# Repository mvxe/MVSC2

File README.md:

# MVSC2 - MV Stepper Controller V2 

Stepper controller using a STM32F411CEU6 and 6x TMC2208-LA-T.  
Intended as a 3D printer controller, or a standalone 6 stepper driver.  
Also has 6 connectors for endstops or servos.  
Includes design with magnetic proximity sensors as endstops using CH912LSR.  

Design files ready for production at JLCPCB (except connectors, TODO).  

NOTE:  
- In the design I use a lower current setting for the stepper driver, which is meant for weaker steppers. Change sense resistor for normal stepper.  
- It is mean to be attached to a 2040 V slot profile, for cooling.  
- Since fabricating this, JLCPCB now supports connectors so this should be updated (hand soldering a USBC is not fun).  
- The power connector requires hand modification: the leads should be shortened such, and the support pins as well as not to portrude from the other side. Apply superglue for extra strength.  
- A compatible Marlin configuration to be added at a later date.

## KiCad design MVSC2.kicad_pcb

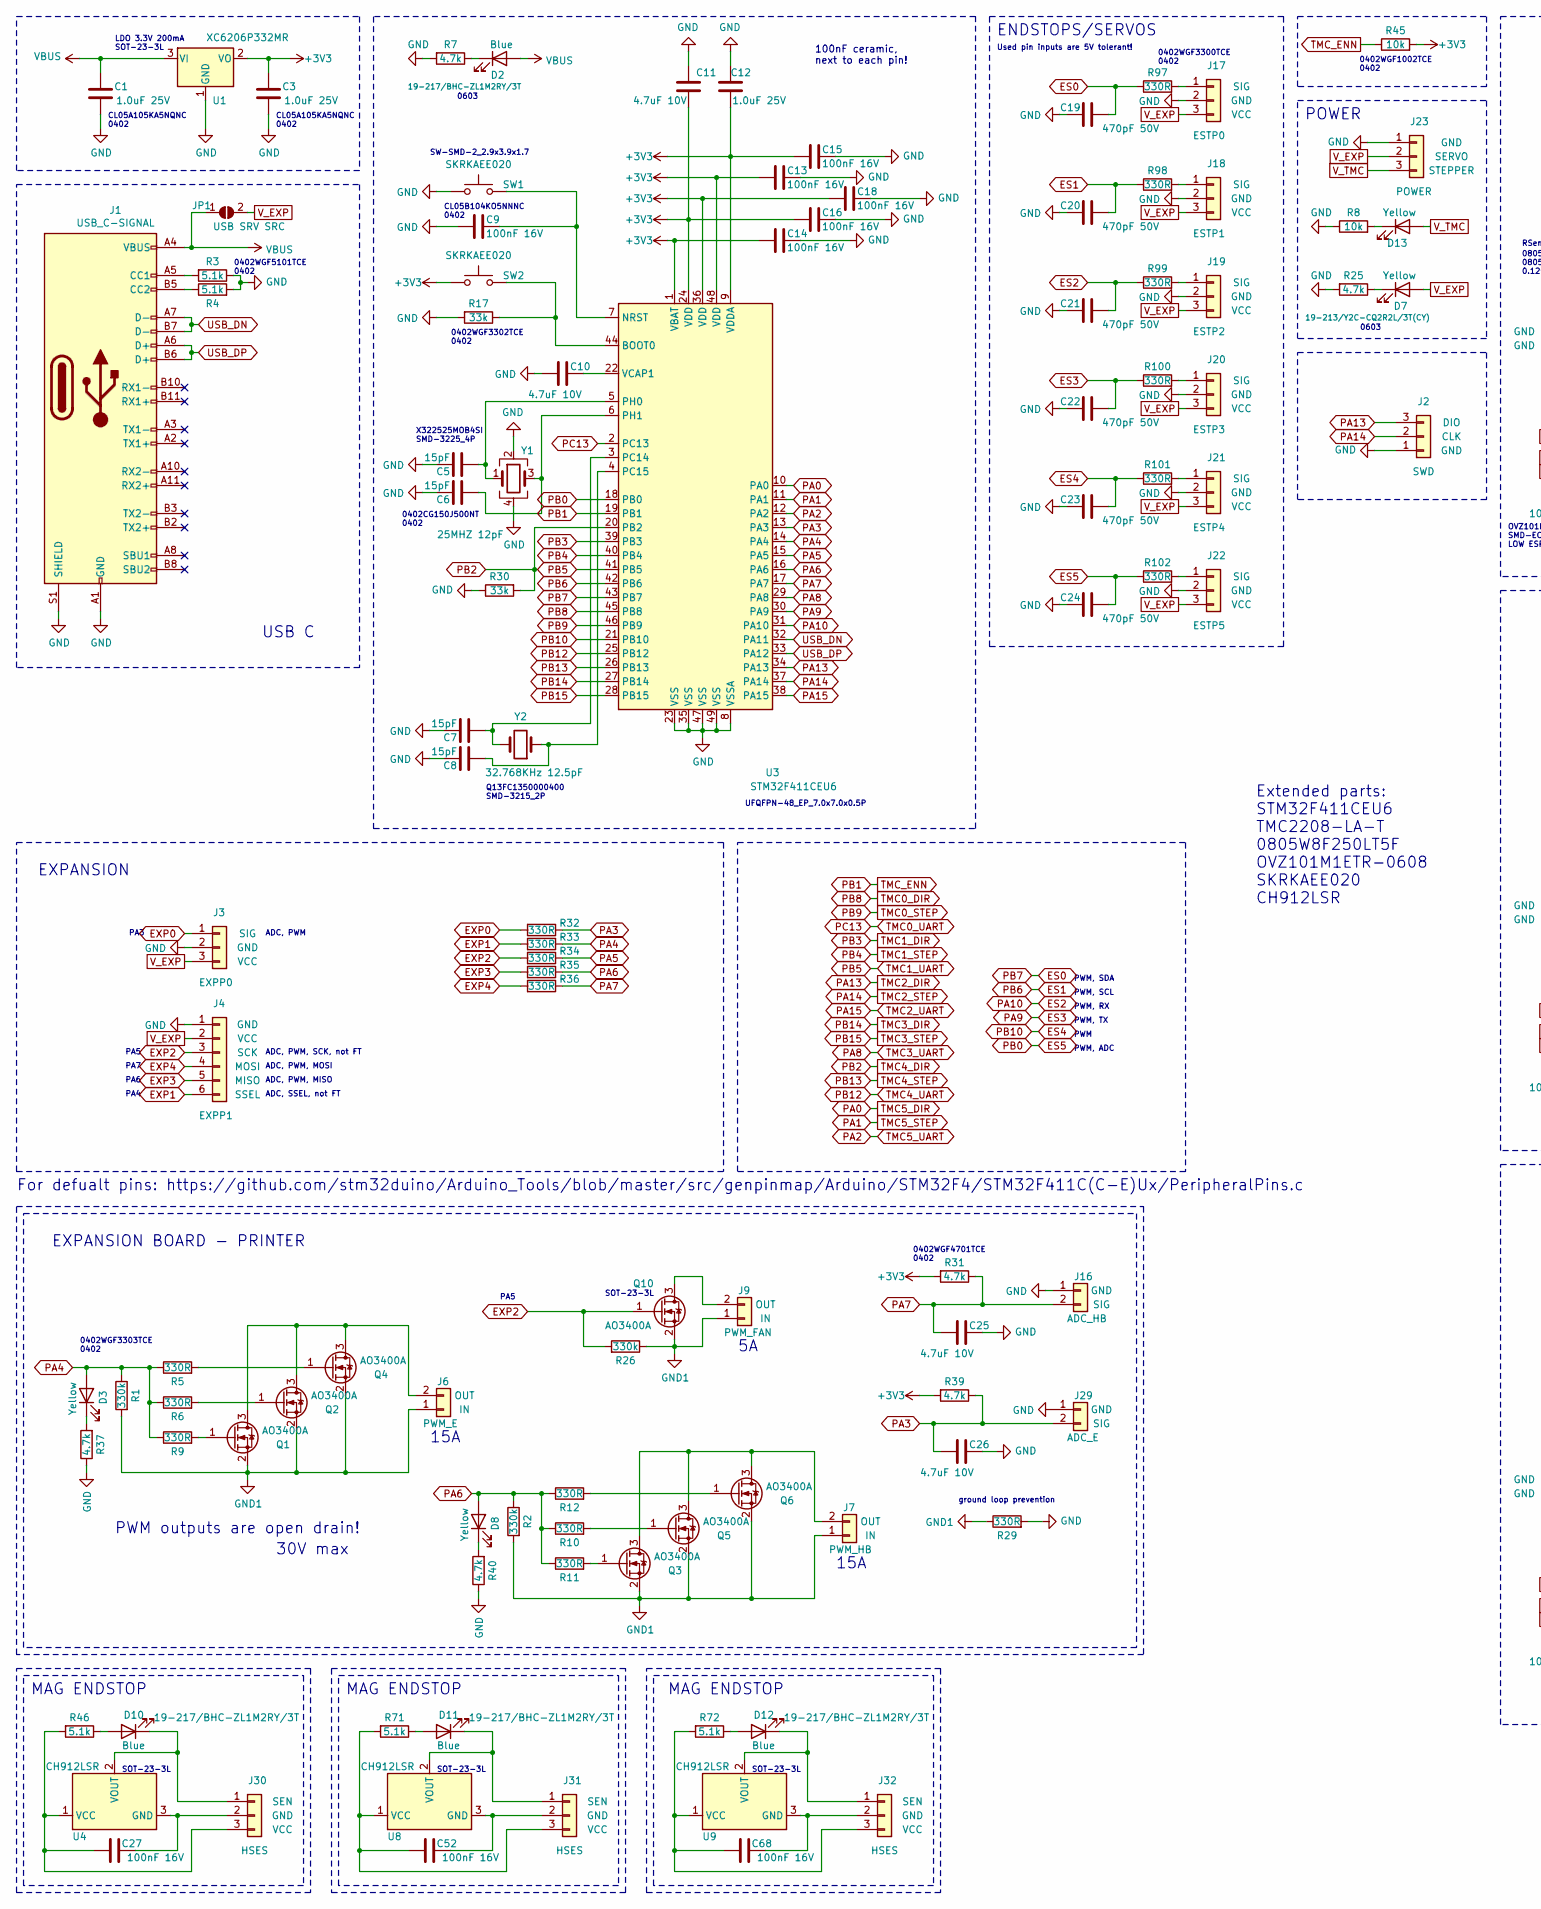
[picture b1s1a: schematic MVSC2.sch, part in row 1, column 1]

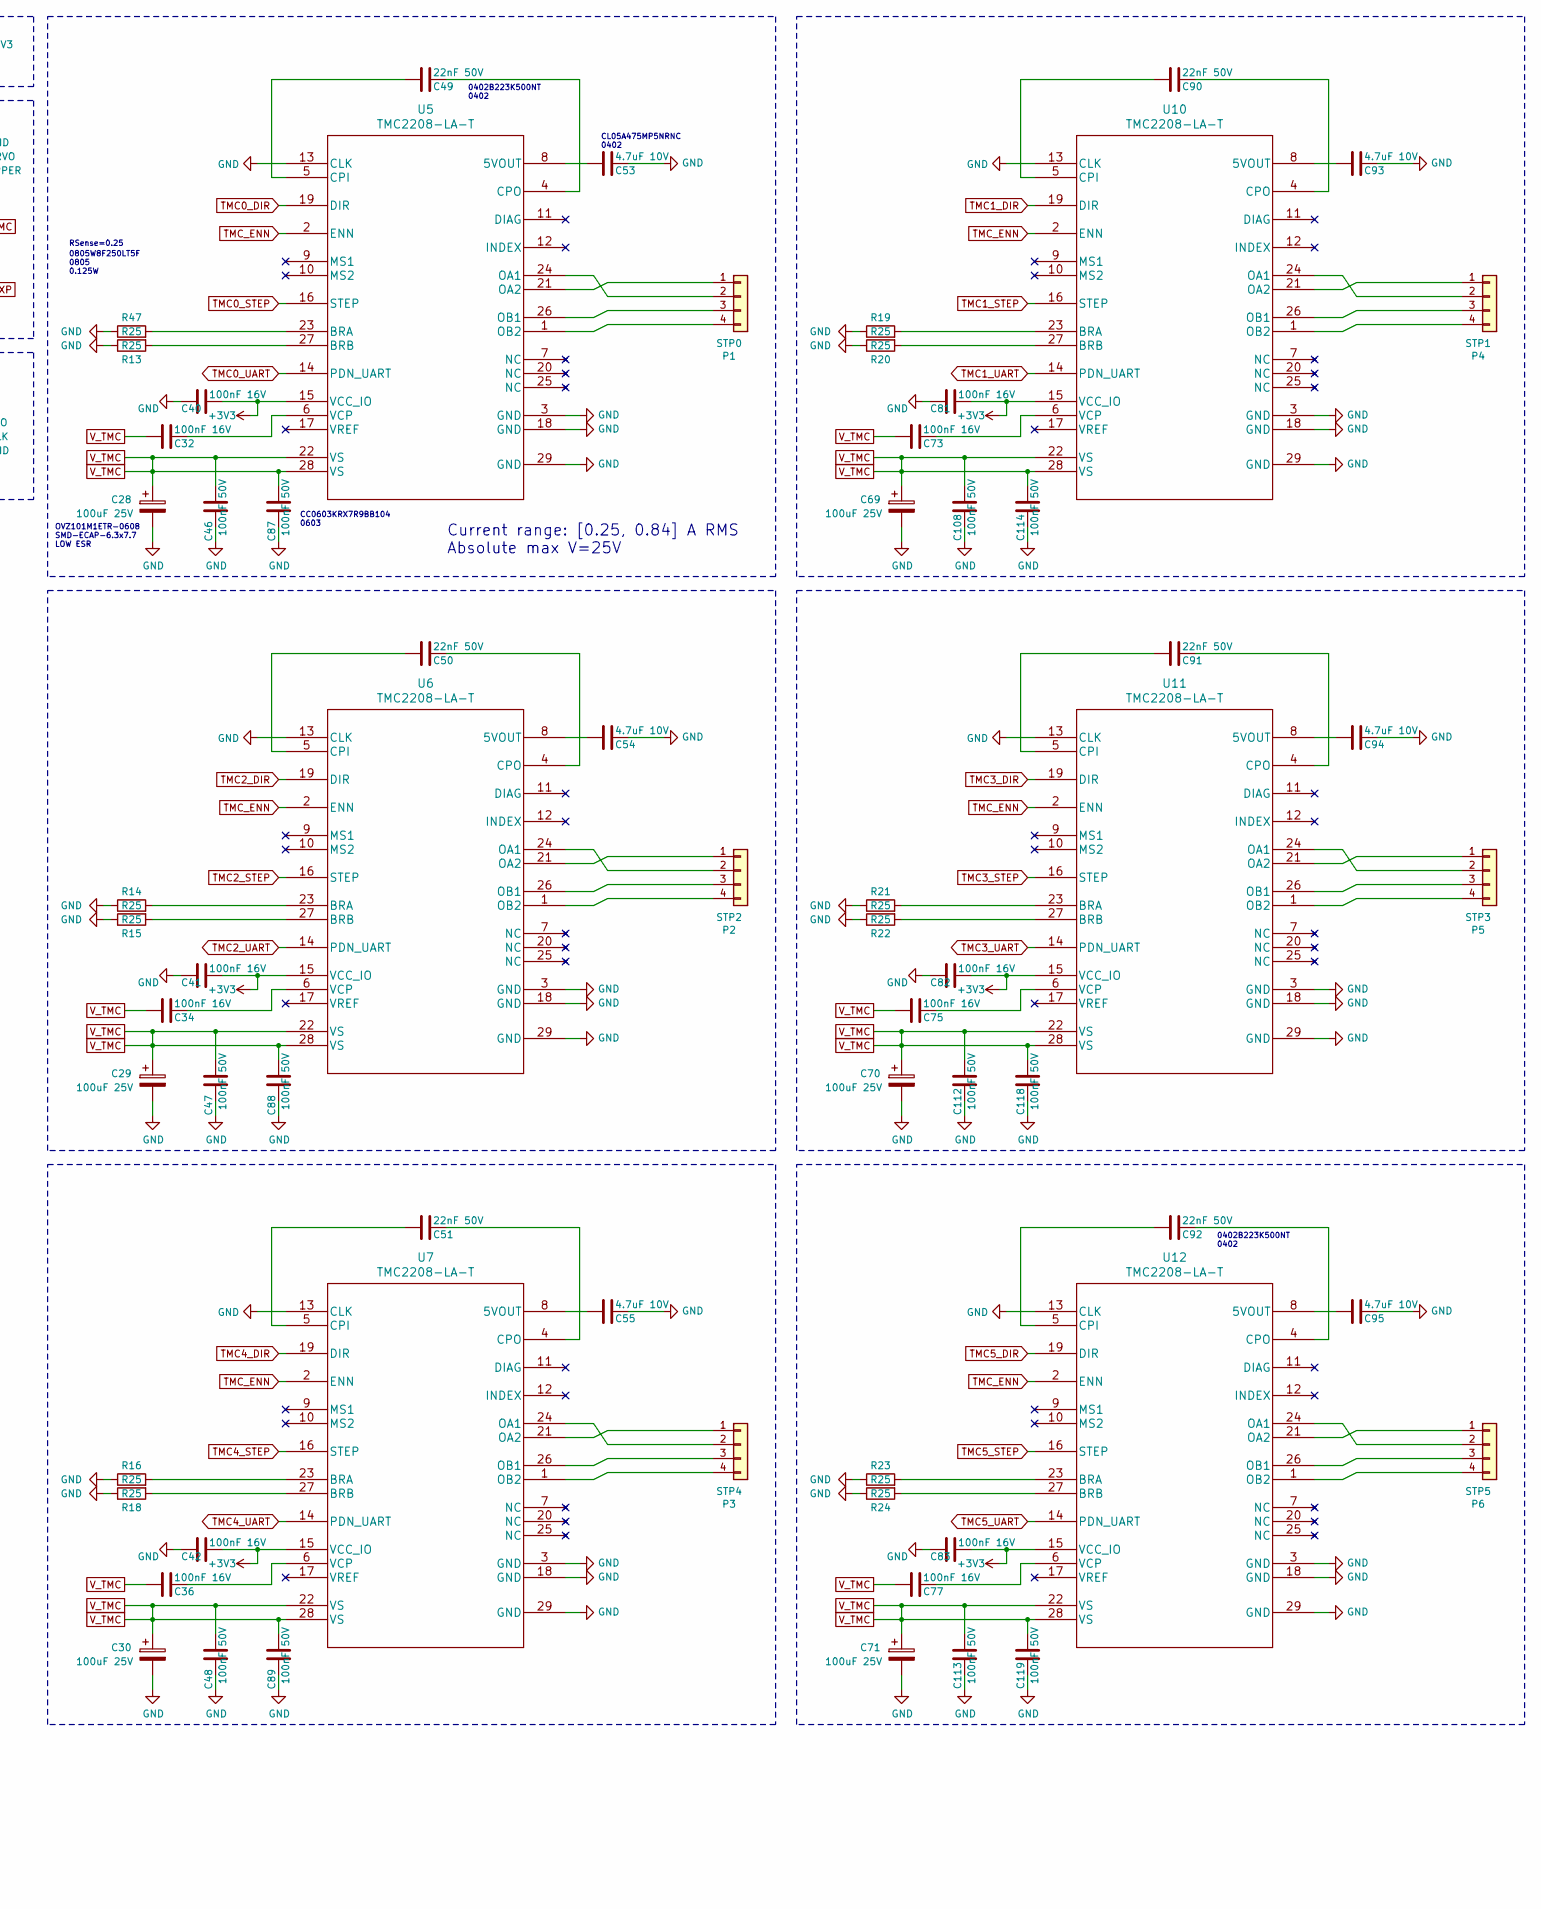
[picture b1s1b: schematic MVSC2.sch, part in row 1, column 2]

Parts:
C1, C3, C12: 1.0uF 25V; C_0402_1005Metric; LCSC C52923
C5, C6, C7, C8: 15pF; C_0402_1005Metric; LCSC C1548
C9, C13, C14, C15, C16, C18, C27, C32, C34, C36, C40, C41, C42, C52, C68, C73, C75, C77, C81, C82, C83: 100nF 16V; C_0402_1005Metric; LCSC C1525
C10, C11, C25, C26, C53, C54, C55, C93, C94, C95: 4.7uF 10V; C_0402_1005Metric; LCSC C23733
C19, C20, C21, C22, C23, C24: 470pF 50V; C_0402_1005Metric; LCSC C1537
C28, C29, C30, C69, C70, C71: 100uF 25V; CP_Elec_6.3x7.7; LCSC C250084
C46, C47, C48, C87, C88, C89, C108, C112, C113, C114, C118, C119: 100nF 50V; C_0603_1608Metric; LCSC C14663
C49, C50, C51, C90, C91, C92: 22nF 50V; C_0402_1005Metric; LCSC C1532
D2, D10, D11, D12: Blue; LED_0603_1608Metric; LCSC C72041
D3, D7, D8, D13: Yellow; LED_0603_1608Metric; LCSC C72038
J1: USB_C-SIGNAL; USB_C_Receptacle_HRO_TYPE-C-31-M-12
J2: SWD; PinHeader_1x03_P2.54mm_Vertical
J3: EXPP0; JST_PH_B3B-PH-K_1x03_P2.00mm_Vertical
J4: EXPP1; JST_PH_B6B-PH-K_1x06_P2.00mm_Vertical
J6: PWM_E; AMASS_XT30U-F_1x02_P5.0mm_Vertical
J7: PWM_HB; AMASS_XT30U-F_1x02_P5.0mm_Vertical
J9: PWM_FAN; JST_PH_B2B-PH-K_1x02_P2.00mm_Vertical
J16: ADC_HB; JST_PH_B2B-PH-K_1x02_P2.00mm_Vertical
J17: ESTP0; JST_PH_B3B-PH-K_1x03_P2.00mm_Vertical
J18: ESTP1; JST_PH_B3B-PH-K_1x03_P2.00mm_Vertical
J19: ESTP2; JST_PH_B3B-PH-K_1x03_P2.00mm_Vertical
J20: ESTP3; JST_PH_B3B-PH-K_1x03_P2.00mm_Vertical
J21: ESTP4; JST_PH_B3B-PH-K_1x03_P2.00mm_Vertical
J22: ESTP5; JST_PH_B3B-PH-K_1x03_P2.00mm_Vertical
J23: POWER; AMASS_MR30PW-M_1x03_P3.50mm_Horizontal
J29: ADC_E; JST_PH_B2B-PH-K_1x02_P2.00mm_Vertical
J30, J31, J32: HSES; JST_PH_B3B-PH-K_1x03_P2.00mm_Vertical
JP1: USB SRV SRC; SolderJumper-2_P1.3mm_Open_TrianglePad1.0x1.5mm
P1: STP0; JST_PH_B4B-PH-K_1x04_P2.00mm_Vertical
P2: STP2; JST_PH_B4B-PH-K_1x04_P2.00mm_Vertical
P3: STP4; JST_PH_B4B-PH-K_1x04_P2.00mm_Vertical
P4: STP1; JST_PH_B4B-PH-K_1x04_P2.00mm_Vertical
P5: STP3; JST_PH_B4B-PH-K_1x04_P2.00mm_Vertical
P6: STP5; JST_PH_B4B-PH-K_1x04_P2.00mm_Vertical
Q1, Q2, Q3, Q4, Q5, Q6, Q10: AO3400A; SOT-23W; LCSC C20917
R1, R2, R26: 330k; R_0402_1005Metric; LCSC C25778
R3, R4, R46, R71, R72: 5.1k; R_0402_1005Metric; LCSC C25905
R5, R6, R9, R10, R11, R12, R29, R32, R33, R34, R35, R36, R97, R98, R99, R100, R101, R102: 330R; R_0402_1005Metric; LCSC C25104
R7, R25, R31, R37, R39, R40: 4.7k; R_0402_1005Metric; LCSC C25900
R8, R45: 10k; R_0402_1005Metric; LCSC C25744
R13, R14, R15, R16, R18, R19, R20, R21, R22, R23, R24, R47: R25; R_0805_2012Metric; LCSC C46216
R17, R30: 33k; R_0402_1005Metric; LCSC C25779
SW1, SW2: SKRKAEE020; SW_Push_SPST_NO_Alps_SKRK; LCSC C115357
U1: XC6206P332MR; SOT-23W; LCSC C5446
U3: STM32F411CEU6; QFN-48-1EP_7x7mm_P0.5mm_EP5.6x5.6mm; LCSC C60420
U4, U8, U9: CH912LSR; SOT-23W; LCSC C455294
U5, U6, U7, U10, U11, U12: TMC2208-LA-T; QFN-28-1EP_5x5mm_P0.5mm_EP3.35x3.35mm_ThermalVias; LCSC C115944
Y1: 25MHZ 12pF; Crystal_SMD_3225-4Pin_3.2x2.5mm; LCSC C9006
Y2: 32.768KHz 12.5pF; Crystal_SMD_3215-2Pin_3.2x1.5mm; LCSC C32346

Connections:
+3V3: C3.2, C11.2, C12.1, C13.2, C14.2, C15.2, C16.2, C18.2, C40.1, C41.1, C42.1, C81.1, C82.1, C83.1, R31.2, R39.2, R45.2, SW2.1, U1.2 (VO), U3.1 (VBAT), U3.9 (VDDA), U3.24 (VDD), U3.36 (VDD), U3.48 (VDD), U5.15 (VCC_IO), U6.15 (VCC_IO), U7.15 (VCC_IO), U10.15 (VCC_IO), U11.15 (VCC_IO), U12.15 (VCC_IO)
ES0: C19.1, R97.1, U3.43 (PB7)
ES1: C20.1, R98.1, U3.42 (PB6)
ES2: C21.1, R99.1, U3.31 (PA10)
ES3: C22.1, R100.1, U3.30 (PA9)
ES4: C23.1, R101.1, U3.21 (PB10)
ES5: C24.1, R102.1, U3.18 (PB0)
EXP0: J3.1, R32.2
EXP1: J4.6, R33.2
EXP2: J4.3, Q10.1 (G), R26.2, R34.2
EXP3: J4.5, R35.2
EXP4: J4.4, R36.2
GND: C1.1, C3.1, C5.1, C6.1, C7.1, C8.1, C9.2, C10.2, C11.1, C12.2, C13.1, C14.1, C15.1, C16.1, C18.1, C19.2, C20.2, C21.2, C22.2, C23.2, C24.2, C25.1, C26.1, C28.2, C29.2, C30.2, C40.2, C41.2, C42.2, C46.1, C47.1, C48.1, C53.1, C54.1, C55.1, C69.2, C70.2, C71.2, C81.2, C82.2, C83.2, C87.1, C88.1, C89.1, C93.1, C94.1, C95.1, C108.1, C112.1, C113.1, C114.1, C118.1, C119.1, J1.A1 (GND), J1.A12 (GND), J1.B1 (GND), J1.B12 (GND), J1.S1 (SHIELD), J2.1, J3.2, J4.1, J16.1, J17.2, J18.2, J19.2, J20.2, J21.2, J22.2, J23.1, J29.1, R3.1, R4.2, R7.2, R8.1, R13.1, R14.1, R15.1, R16.1, R17.2, R18.1, R19.1, R20.1, R21.1, R22.1, R23.1, R24.1, R25.2, R29.2, R30.1, R37.1, R40.1, R47.1, SW1.1, U1.1 (GND), U3.8 (VSSA), U3.23 (VSS), U3.35 (VSS), U3.47 (VSS), U3.49 (VSS), U5.3 (GND), U5.13 (CLK), U5.18 (GND), U5.29 (GND), U6.3 (GND), U6.13 (CLK), U6.18 (GND), U6.29 (GND), U7.3 (GND), U7.13 (CLK), U7.18 (GND), U7.29 (GND), U10.3 (GND), U10.13 (CLK), U10.18 (GND), U10.29 (GND), U11.3 (GND), U11.13 (CLK), U11.18 (GND), U11.29 (GND), U12.3 (GND), U12.13 (CLK), U12.18 (GND), U12.29 (GND), Y1.2, Y1.4
GND1: J6.1, J7.1, J9.1, Q1.2 (S), Q2.2 (S), Q3.2 (S), Q4.2 (S), Q5.2 (S), Q6.2 (S), Q10.2 (S), R1.2, R2.2, R26.1, R29.1
unnamed: C5.2, U3.5 (PH0), Y1.1
unnamed: C6.2, U3.6 (PH1), Y1.3
unnamed: C7.2, U3.3 (PC14), Y2.2
unnamed: C8.2, U3.4 (PC15), Y2.1
unnamed: C9.1, SW1.2, U3.7 (NRST)
unnamed: C10.1, U3.22 (VCAP1)
unnamed: C27.1, J30.3, R46.2, U4.1 (VCC)
unnamed: C27.2, J30.2, U4.3 (GND)
unnamed: C32.1, U5.6 (VCP)
unnamed: C34.1, U6.6 (VCP)
unnamed: C36.1, U7.6 (VCP)
unnamed: C49.1, U5.4 (CPO)
unnamed: C49.2, U5.5 (CPI)
unnamed: C50.1, U6.4 (CPO)
unnamed: C50.2, U6.5 (CPI)
unnamed: C51.1, U7.4 (CPO)
unnamed: C51.2, U7.5 (CPI)
unnamed: C52.1, J31.3, R71.2, U8.1 (VCC)
unnamed: C52.2, J31.2, U8.3 (GND)
unnamed: C53.2, U5.8 (5VOUT)
unnamed: C54.2, U6.8 (5VOUT)
unnamed: C55.2, U7.8 (5VOUT)
unnamed: C68.1, J32.3, R72.2, U9.1 (VCC)
unnamed: C68.2, J32.2, U9.3 (GND)
unnamed: C73.1, U10.6 (VCP)
unnamed: C75.1, U11.6 (VCP)
unnamed: C77.1, U12.6 (VCP)
unnamed: C90.1, U10.4 (CPO)
unnamed: C90.2, U10.5 (CPI)
unnamed: C91.1, U11.4 (CPO)
unnamed: C91.2, U11.5 (CPI)
unnamed: C92.1, U12.4 (CPO)
unnamed: C92.2, U12.5 (CPI)
unnamed: C93.2, U10.8 (5VOUT)
unnamed: C94.2, U11.8 (5VOUT)
unnamed: C95.2, U12.8 (5VOUT)
unnamed: D2.1 (K), R7.1
unnamed: D3.1 (K), R37.2
unnamed: D7.1 (K), R25.1
unnamed: D8.1 (K), R40.2
unnamed: D10.1 (K), J30.1, U4.2 (VOUT)
unnamed: D10.2 (A), R46.1
unnamed: D11.1 (K), J31.1, U8.2 (VOUT)
unnamed: D11.2 (A), R71.1
unnamed: D12.1 (K), J32.1, U9.2 (VOUT)
unnamed: D12.2 (A), R72.1
unnamed: D13.1 (K), R8.2
unnamed: J1.A5 (CC1), R3.2
unnamed: J1.B5 (CC2), R4.1
unnamed: J6.2, Q1.3 (D), Q2.3 (D), Q4.3 (D)
unnamed: J7.2, Q3.3 (D), Q5.3 (D), Q6.3 (D)
unnamed: J9.2, Q10.3 (D)
unnamed: J17.1, R97.2
unnamed: J18.1, R98.2
unnamed: J19.1, R99.2
unnamed: J20.1, R100.2
unnamed: J21.1, R101.2
unnamed: J22.1, R102.2
unnamed: P1.1, U5.21 (OA2)
unnamed: P1.2, U5.24 (OA1)
unnamed: P1.3, U5.26 (OB1)
unnamed: P1.4, U5.1 (OB2)
unnamed: P2.1, U6.21 (OA2)
unnamed: P2.2, U6.24 (OA1)
unnamed: P2.3, U6.26 (OB1)
unnamed: P2.4, U6.1 (OB2)
unnamed: P3.1, U7.21 (OA2)
unnamed: P3.2, U7.24 (OA1)
unnamed: P3.3, U7.26 (OB1)
unnamed: P3.4, U7.1 (OB2)
unnamed: P4.1, U10.21 (OA2)
unnamed: P4.2, U10.24 (OA1)
unnamed: P4.3, U10.26 (OB1)
unnamed: P4.4, U10.1 (OB2)
unnamed: P5.1, U11.21 (OA2)
unnamed: P5.2, U11.24 (OA1)
unnamed: P5.3, U11.26 (OB1)
unnamed: P5.4, U11.1 (OB2)
unnamed: P6.1, U12.21 (OA2)
unnamed: P6.2, U12.24 (OA1)
unnamed: P6.3, U12.26 (OB1)
unnamed: P6.4, U12.1 (OB2)
unnamed: Q1.1 (G), R9.2
unnamed: Q2.1 (G), R6.2
unnamed: Q3.1 (G), R11.2
unnamed: Q4.1 (G), R5.2
unnamed: Q5.1 (G), R10.2
unnamed: Q6.1 (G), R12.2
unnamed: R13.2, U5.27 (BRB)
unnamed: R14.2, U6.23 (BRA)
unnamed: R15.2, U6.27 (BRB)
unnamed: R16.2, U7.23 (BRA)
unnamed: R17.1, SW2.2, U3.44 (BOOT0)
unnamed: R18.2, U7.27 (BRB)
unnamed: R19.2, U10.23 (BRA)
unnamed: R20.2, U10.27 (BRB)
unnamed: R21.2, U11.23 (BRA)
unnamed: R22.2, U11.27 (BRB)
unnamed: R23.2, U12.23 (BRA)
unnamed: R24.2, U12.27 (BRB)
unnamed: R47.2, U5.23 (BRA)
PA0: U3.10 (PA0), U12.19 (DIR)
PA1: U3.11 (PA1), U12.16 (STEP)
PA2: U3.12 (PA2), U12.14 (PDN_UART)
PA3: C26.2, J29.2, R32.1, R39.1, U3.13 (PA3)
PA4: D3.2 (A), R1.1, R5.1, R6.1, R9.1, R33.1, U3.14 (PA4)
PA5: R34.1, U3.15 (PA5)
PA6: D8.2 (A), R2.1, R10.1, R11.1, R12.1, R35.1, U3.16 (PA6)
PA7: C25.2, J16.2, R31.1, R36.1, U3.17 (PA7)
PA8: U3.29 (PA8), U11.14 (PDN_UART)
PA13: J2.3, U3.34 (PA13), U6.19 (DIR)
PA14: J2.2, U3.37 (PA14), U6.16 (STEP)
PA15: U3.38 (PA15), U6.14 (PDN_UART)
PB1: R45.1, U3.19 (PB1), U5.2 (ENN), U6.2 (ENN), U7.2 (ENN), U10.2 (ENN), U11.2 (ENN), U12.2 (ENN)
PB2: R30.2, U3.20 (PB2), U7.19 (DIR)
PB3: U3.39 (PB3), U10.19 (DIR)
PB4: U3.40 (PB4), U10.16 (STEP)
PB5: U3.41 (PB5), U10.14 (PDN_UART)
PB8: U3.45 (PB8), U5.19 (DIR)
PB9: U3.46 (PB9), U5.16 (STEP)
PB12: U3.25 (PB12), U7.14 (PDN_UART)
PB13: U3.26 (PB13), U7.16 (STEP)
PB14: U3.27 (PB14), U11.19 (DIR)
PB15: U3.28 (PB15), U11.16 (STEP)
PC13: U3.2 (PC13), U5.14 (PDN_UART)
USB_DN: J1.A7 (D-), J1.B7 (D-), U3.32 (PA11)
USB_DP: J1.A6 (D+), J1.B6 (D+), U3.33 (PA12)
VBUS: C1.2, D2.2 (A), J1.A4 (VBUS), J1.A9 (VBUS), J1.B4 (VBUS), J1.B9 (VBUS), JP1.1 (A), U1.3 (VI)
V_EXP: D7.2 (A), J3.3, J4.2, J17.3, J18.3, J19.3, J20.3, J21.3, J22.3, J23.2, JP1.2 (B)
V_TMC: C28.1, C29.1, C30.1, C32.2, C34.2, C36.2, C46.2, C47.2, C48.2, C69.1, C70.1, C71.1, C73.2, C75.2, C77.2, C87.2, C88.2, C89.2, C108.2, C112.2, C113.2, C114.2, C118.2, C119.2, D13.2 (A), J23.3, U5.22 (VS), U5.28 (VS), U6.22 (VS), U6.28 (VS), U7.22 (VS), U7.28 (VS), U10.22 (VS), U10.28 (VS), U11.22 (VS), U11.28 (VS), U12.22 (VS), U12.28 (VS)

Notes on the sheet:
100nF ceramic, next to each pin!
CL05A105KA5NQNC 0402
LDO 3.3V 200mA SOT-23-3L
X322525MOB4SI SMD-3225_4P
Q13FC1350000400 SMD-3215_2P
Extended parts: STM32F411CEU6 TMC2208-LA-T 0805W8F250LT5F OVZ101M1ETR-0608 SKRKAEE020 CH912LSR
UFQFPN-48_EP_7.0x7.0x0.5P
CL05B104KO5NNNC 0402
0402CG150J500NT 0402
0402WGF3302TCE 0402
0402WGF5101TCE 0402
0402WGF1002TCE 0402
Current range: [0.25, 0.84] A RMS Absolute max V=25V
OVZ101M1ETR-0608 SMD-ECAP-6.3x7.7 LOW ESR
CL05A475MP5NRNC 0402
0402B223K500NT 0402
CC0603KRX7R9BB104 0603
SW-SMD-2_2.9x3.9x1.7
SOT-23-3L
0402WGF4701TCE 0402
0805W8F250LT5F 0805 0.125W
RSense=0.25
POWER
EXPANSION
USB C
0402WGF3300TCE 0402
0603
For defualt pins: https://github.com/stm32duino/Arduino_Tools/blob/master/src/genpinmap/Arduino/STM32F4/STM32F411C(C-E)Ux/PeripheralPins.c
EXPANSION BOARD - PRINTER
15A
0402WGF3303TCE 0402
MAG ENDSTOP
ENDSTOPS/SERVOS
PWM, SDA
PWM, SCL
ADC, PWM, MOSI
ADC, PWM, MISO
ADC, PWM, SCK, not FT
PWM, RX
PWM, TX

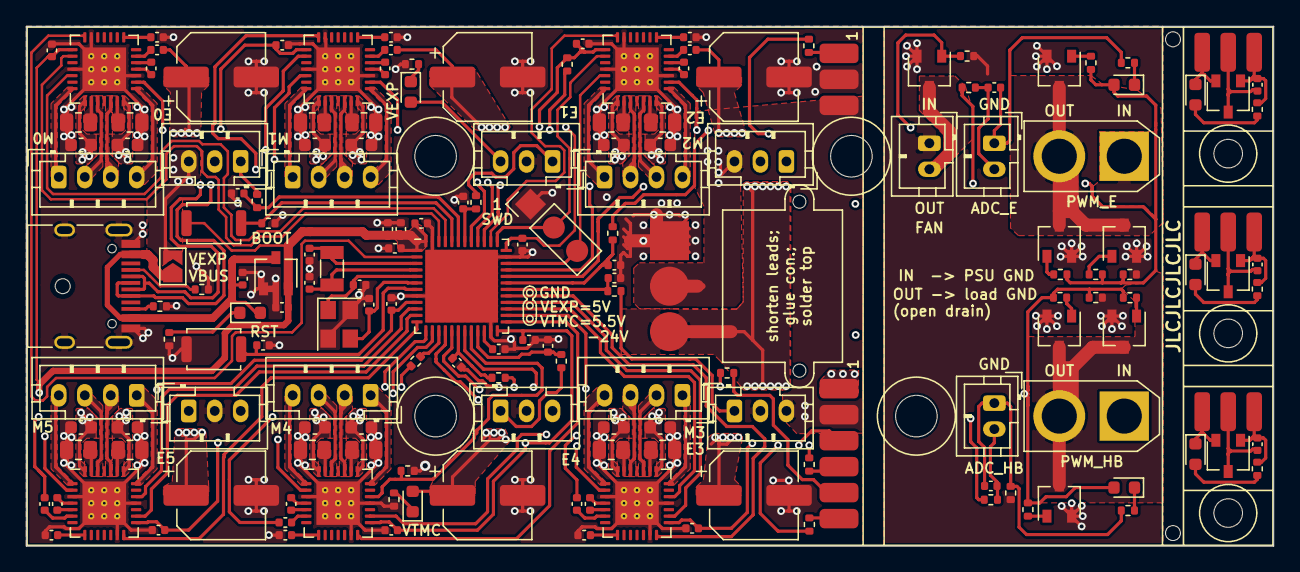
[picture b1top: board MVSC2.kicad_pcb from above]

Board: 4 copper layers, 96.0 x 40.0 mm, 175 parts (0 on the bottom side), 144 nets.

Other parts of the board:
tooling: MountingHole_2.2mm_M2
tooling#2, tooling#3: MountingHole_2.2mm_M2

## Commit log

2022-12-20 panelized but too expensive for jlcpcb
2022-12-20 added readme
2022-12-20 working
2022-12-20 going to rearrange everything
2022-12-20 working layout - needs tripple checking
2022-12-20 working version with mosfets
2022-12-20 final, ordered
2022-12-20 fixed all drc errors and checked zones; still TODO: check everything
2022-12-20 partial
